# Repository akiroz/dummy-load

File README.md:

## Dummy Load

A dummy electronic loading that dumps power into 8 independently driven BJTs (Up to 1000W)

## Firmware

Written using mbedOS with PlatformIO.

```
$ pio run -t upload
```

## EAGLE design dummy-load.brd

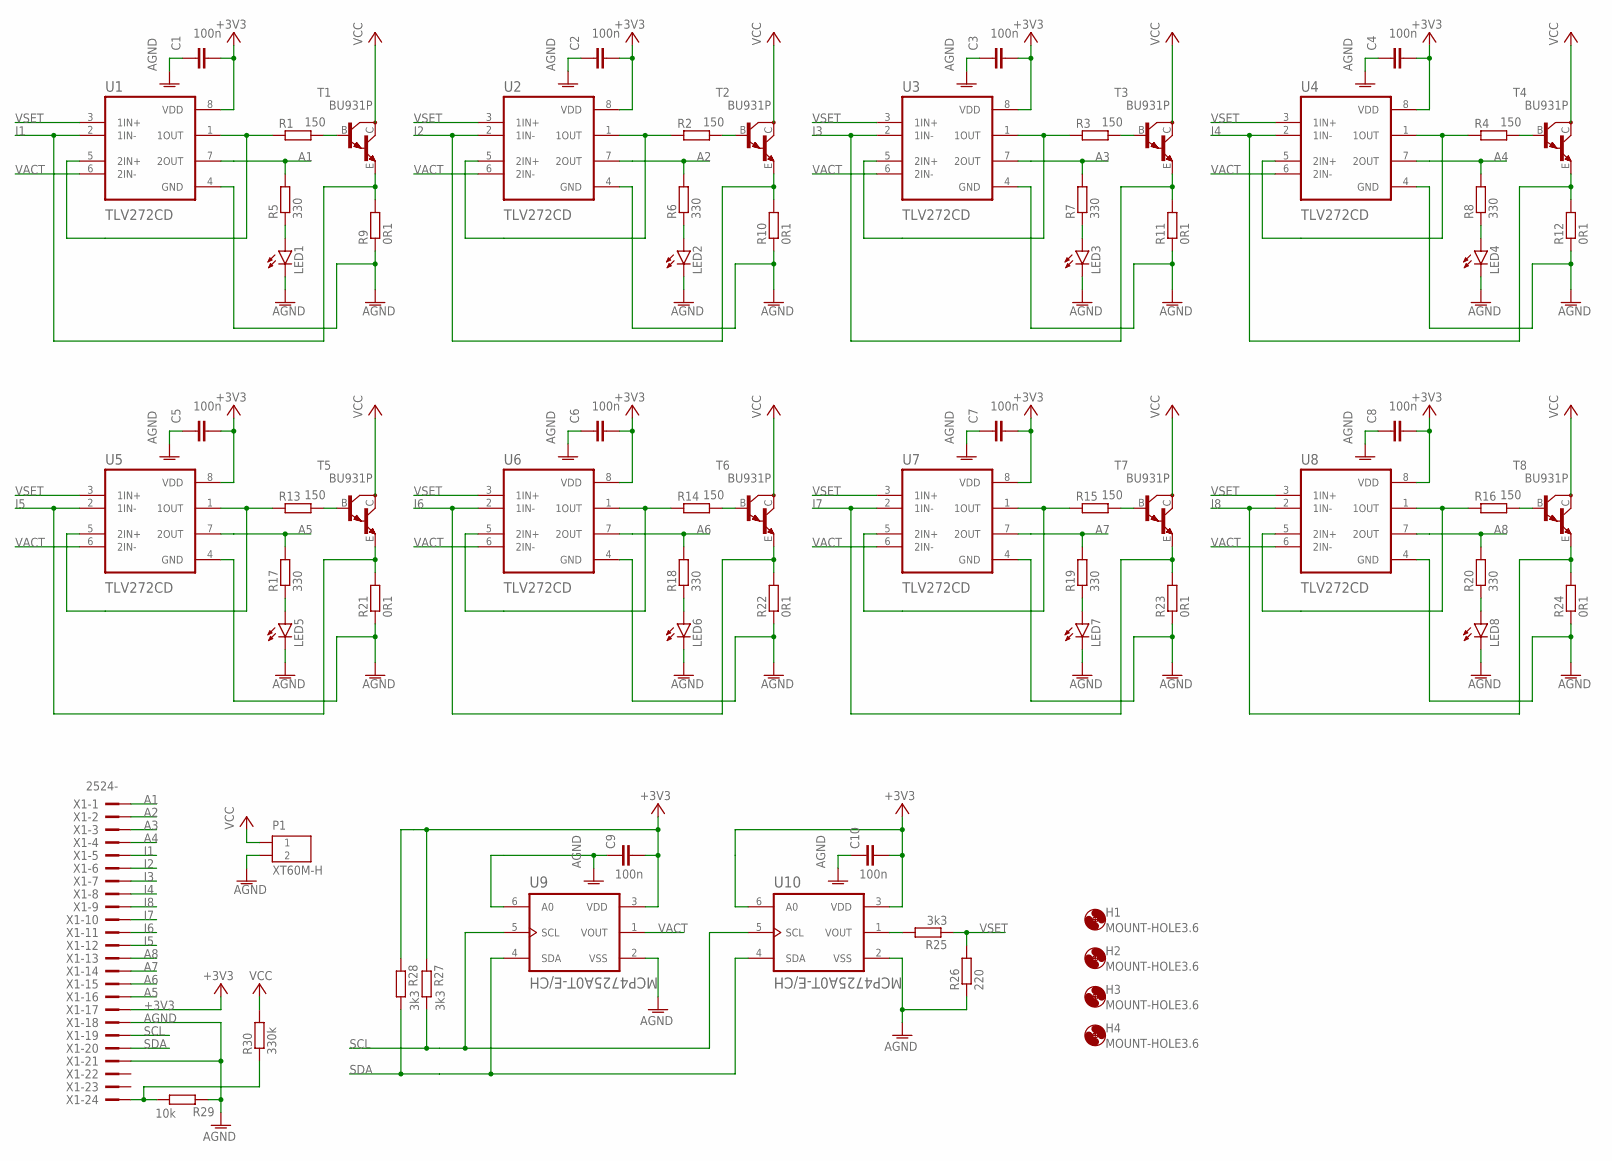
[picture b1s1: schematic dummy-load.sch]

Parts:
C1, C2, C3, C4, C5, C6, C7, C8, C9, C10: 100n; C0805
H1, H2, H3, H4: MOUNT-HOLE3.6; 3,6
LED1, LED2, LED3, LED4, LED5, LED6, LED7, LED8: LEDCHIP-LED0603; CHIP-LED0603
P1: XT60M-H
R1, R2, R3, R4, R13, R14, R15, R16: 150; R0805
R5, R6, R7, R8, R17, R18, R19, R20: 330; R0805
R9, R10, R11, R12, R21, R22, R23, R24: 0R1; R2512
R25, R27, R28: 3k3; R0805
R26: 220; R0805
R29: 10k; R0805
R30: 330k; R0805
T1, T2, T3, T4, T5, T6, T7, T8: BU931P; TO-247-H
U1, U2, U3, U4, U5, U6, U7, U8: TLV272CD; SOIC127P599X175-8N
U9, U10: MCP4725A0T-E/CH; SOT95P270X145-6N
X1: 2524-; PAK100/2500-24

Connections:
+3V3: C1.2, C2.2, C3.2, C4.2, C5.2, C6.2, C7.2, C8.2, C9.2, C10.2, R27.1, R28.1, U1.8 (VDD), U2.8 (VDD), U3.8 (VDD), U4.8 (VDD), U5.8 (VDD), U6.8 (VDD), U7.8 (VDD), U8.8 (VDD), U9.3 (VDD), U10.3 (VDD), U10.6 (A0), X1.17
A1: R5.2, U1.7 (2OUT), X1.1
A2: R6.2, U2.7 (2OUT), X1.2
A3: R7.2, U3.7 (2OUT), X1.3
A4: R8.2, U4.7 (2OUT), X1.4
A5: R17.2, U5.7 (2OUT), X1.16
A6: R18.2, U6.7 (2OUT), X1.15
A7: R19.2, U7.7 (2OUT), X1.14
A8: R20.2, U8.7 (2OUT), X1.13
AGND: C1.1, C2.1, C3.1, C4.1, C5.1, C6.1, C7.1, C8.1, C9.1, C10.1, LED1.C, LED2.C, LED3.C, LED4.C, LED5.C, LED6.C, LED7.C, LED8.C, P1.- (2), R9.1, R10.1, R11.1, R12.1, R21.1, R22.1, R23.1, R24.1, R26.1, R29.1, U1.4 (GND), U2.4 (GND), U3.4 (GND), U4.4 (GND), U5.4 (GND), U6.4 (GND), U7.4 (GND), U8.4 (GND), U9.2 (VSS), U9.6 (A0), U10.2 (VSS), X1.18, X1.21
I1: R9.2, T1.E, U1.2 (1IN-), X1.5
I2: R10.2, T2.E, U2.2 (1IN-), X1.6
I3: R11.2, T3.E, U3.2 (1IN-), X1.7
I4: R12.2, T4.E, U4.2 (1IN-), X1.8
I5: R21.2, T5.E, U5.2 (1IN-), X1.12
I6: R22.2, T6.E, U6.2 (1IN-), X1.11
I7: R23.2, T7.E, U7.2 (1IN-), X1.10
I8: R24.2, T8.E, U8.2 (1IN-), X1.9
unnamed: R29.2, R30.1, X1.24
unnamed: LED5.A, R17.1
unnamed: LED6.A, R18.1
unnamed: R14.2, T6.B
unnamed: R14.1, U6.1 (1OUT), U6.5 (2IN+)
unnamed: LED7.A, R19.1
unnamed: R15.2, T7.B
unnamed: R13.2, T5.B
unnamed: R13.1, U5.1 (1OUT), U5.5 (2IN+)
unnamed: R15.1, U7.1 (1OUT), U7.5 (2IN+)
unnamed: LED8.A, R20.1
unnamed: R16.2, T8.B
unnamed: R16.1, U8.1 (1OUT), U8.5 (2IN+)
unnamed: LED1.A, R5.1
unnamed: R1.2, T1.B
unnamed: R1.1, U1.1 (1OUT), U1.5 (2IN+)
unnamed: LED2.A, R6.1
unnamed: R2.2, T2.B
unnamed: R2.1, U2.1 (1OUT), U2.5 (2IN+)
unnamed: LED3.A, R7.1
unnamed: R3.2, T3.B
unnamed: R3.1, U3.1 (1OUT), U3.5 (2IN+)
unnamed: LED4.A, R8.1
unnamed: R4.2, T4.B
unnamed: R4.1, U4.1 (1OUT), U4.5 (2IN+)
unnamed: R25.2, U10.1 (VOUT)
SCL: R27.2, U9.5 (SCL), U10.5 (SCL), X1.19
SDA: R28.2, U9.4 (SDA), U10.4 (SDA), X1.20
VACT: U1.6 (2IN-), U2.6 (2IN-), U3.6 (2IN-), U4.6 (2IN-), U5.6 (2IN-), U6.6 (2IN-), U7.6 (2IN-), U8.6 (2IN-), U9.1 (VOUT)
VCC: P1.+ (1), R30.2, T1.C, T2.C, T3.C, T4.C, T5.C, T6.C, T7.C, T8.C
VSET: R25.1, R26.2, U1.3 (1IN+), U2.3 (1IN+), U3.3 (1IN+), U4.3 (1IN+), U5.3 (1IN+), U6.3 (1IN+), U7.3 (1IN+), U8.3 (1IN+)

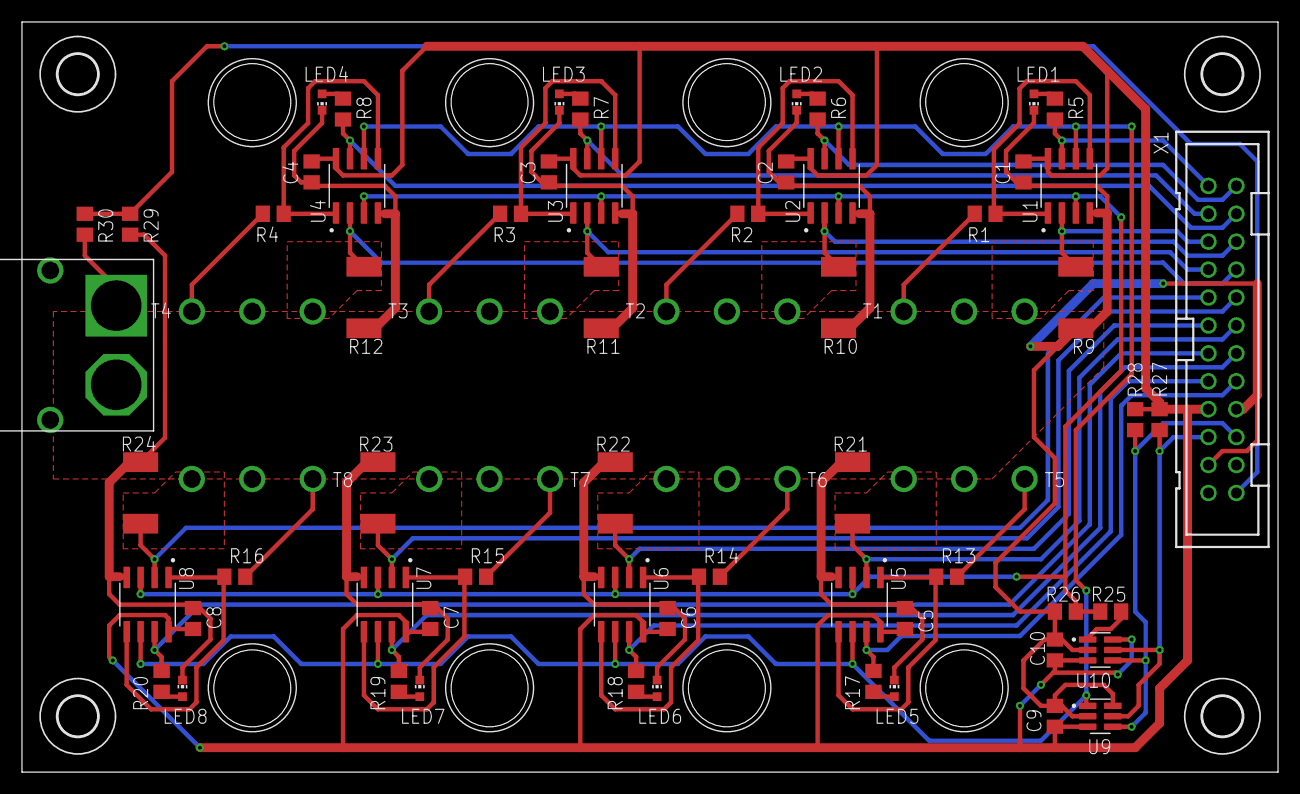
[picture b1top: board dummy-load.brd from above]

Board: 2 copper layers, 114.3 x 68.2 mm, 72 parts (0 on the bottom side), 49 nets.

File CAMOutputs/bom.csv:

Comment,Designator,Footprint,LCSC Part #（optional）
100n,"C1, C2, C3, C4, C5, C6, C7, C8, C9, C10",C0805,C49678
0R1,"R9, R10, R11, R12, R21, R22, R23, R24",R2512,C76282
150R,"R1, R2, R3, R4, R13, R14, R15, R16",R0805,C17471
220R,R26,R0805,C17557
330R,"R5, R6, R7, R8, R17, R18, R19, R20",R0805,C17630
3k3,"R25, R27, R28",R0805,C26010
10k,R29,R0805,C17414
330k,R30,R0805,C17629
MCP4725A0T-E/CH,"U9, U10",SOT-23-6,C144198
TLV272CD,"U1, U2, U3, U4, U5, U6, U7, U8",SO8,C398914
Yellow,"LED1, LED2, LED3, LED4, LED5, LED6, LED7, LED8",CHIPLED_0603,C72038

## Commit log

2021-05-02 init
2021-05-02 PCB routing
2021-05-11 Add XT60 connector
2021-05-18 test firmware
